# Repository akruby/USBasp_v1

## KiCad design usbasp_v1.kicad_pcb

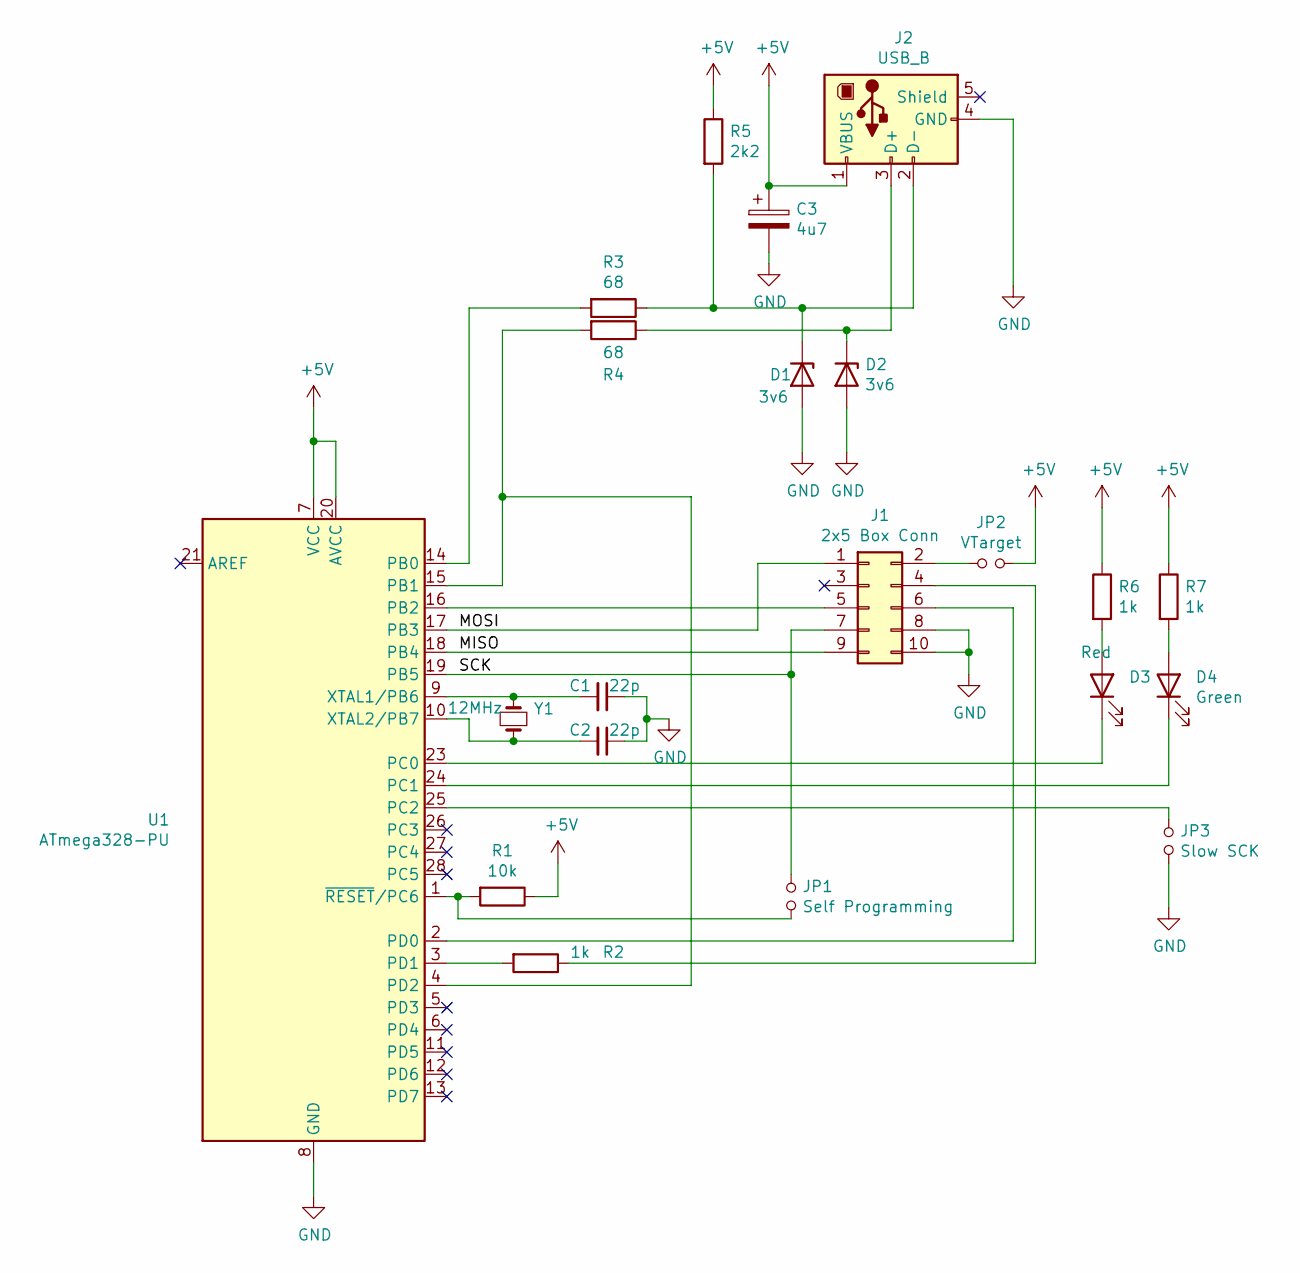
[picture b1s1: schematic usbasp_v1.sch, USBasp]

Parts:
C1, C2: 22p; C_Disc_D5.0mm_W2.5mm_P2.50mm
C3: 4u7; CP_Radial_D4.0mm_P1.50mm
D1, D2: 3v6; D_A-405_P7.62mm_Horizontal
D3: Red; LED_D3.0mm
D4: Green; LED_D3.0mm
J1: 2x5 Box Conn; IDC-Header_2x05_P2.54mm_Vertical
J2: USB_B; USB_B_OST_USB-B1HSxx_Horizontal
JP1: Self Programming; PinHeader_1x02_P2.54mm_Vertical
JP2: VTarget; PinHeader_1x02_P2.54mm_Vertical
JP3: Slow SCK; PinHeader_1x02_P2.54mm_Vertical
R1: 10k; R_Axial_DIN0207_L6.3mm_D2.5mm_P7.62mm_Horizontal
R2, R6, R7: 1k; R_Axial_DIN0207_L6.3mm_D2.5mm_P7.62mm_Horizontal
R3, R4: 68; R_Axial_DIN0207_L6.3mm_D2.5mm_P7.62mm_Horizontal
R5: 2k2; R_Axial_DIN0207_L6.3mm_D2.5mm_P7.62mm_Horizontal
U1: ATmega328-PU; DIP-28_W7.62mm_LongPads
Y1: 12MHz; Crystal_HC49-U_Vertical

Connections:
+5V: C3.1, J2.1 (VBUS), JP2.2, R1.1, R5.1, R6.1, R7.1, U1.7 (VCC), U1.20 (AVCC)
/MISO: J1.9, U1.18 (PB4)
/MOSI: J1.1, U1.17 (PB3)
/SCK: J1.7, JP1.1, U1.19 (PB5)
GND: C1.1, C2.1, C3.2, D1.2 (A), D2.2 (A), J1.8, J1.10, J2.4 (GND), JP3.2, U1.8 (GND), U1.22 (GND)
unnamed: C1.2, U1.9 (XTAL1/PB6), Y1.1
unnamed: C2.2, U1.10 (XTAL2/PB7), Y1.2
unnamed: D1.1 (K), J2.2 (D-), R3.1, R5.2
unnamed: D2.1 (K), J2.3 (D+), R4.1
unnamed: D3.1 (K), U1.23 (PC0)
unnamed: D3.2 (A), R6.2
unnamed: D4.1 (K), U1.24 (PC1)
unnamed: D4.2 (A), R7.2
unnamed: J1.2, JP2.1
unnamed: J1.4, R2.1
unnamed: J1.5, U1.16 (PB2)
unnamed: J1.6, U1.2 (PD0)
unnamed: JP1.2, R1.2, U1.1 (~RESET~/PC6)
unnamed: JP3.1, U1.25 (PC2)
unnamed: R2.2, U1.3 (PD1)
unnamed: R3.2, U1.14 (PB0)
unnamed: R4.2, U1.4 (PD2), U1.15 (PB1)

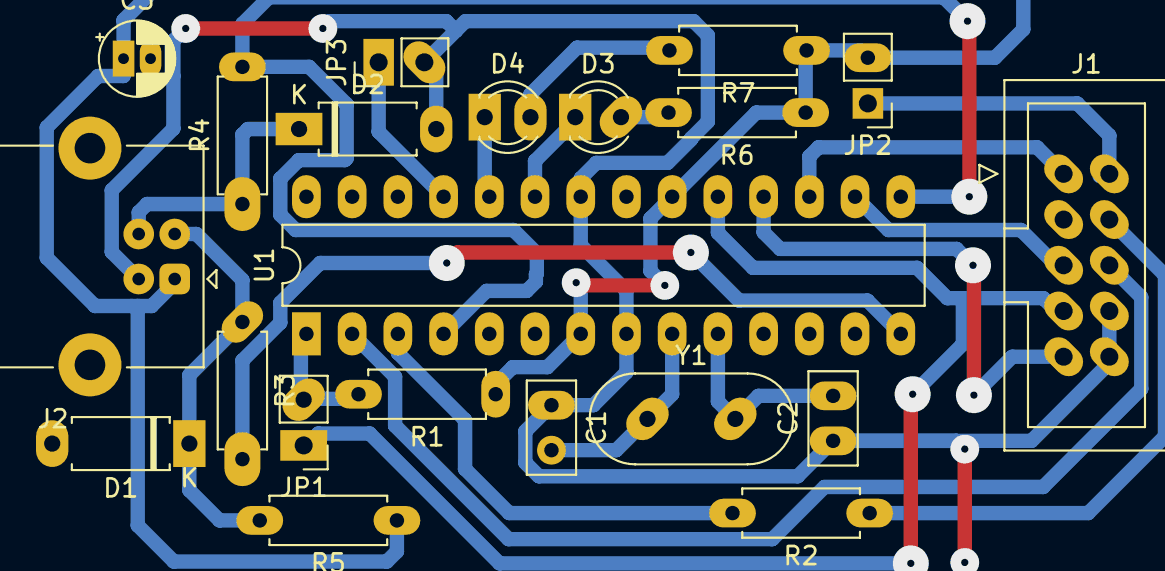
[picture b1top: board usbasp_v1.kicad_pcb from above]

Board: 2 copper layers, 21 parts (0 on the bottom side), 22 nets.

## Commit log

2020-11-28 Generated drill and gerber files
2020-11-29 Increased pad sizes for better toner transfer
2020-11-30 Corrected ground plane connection
